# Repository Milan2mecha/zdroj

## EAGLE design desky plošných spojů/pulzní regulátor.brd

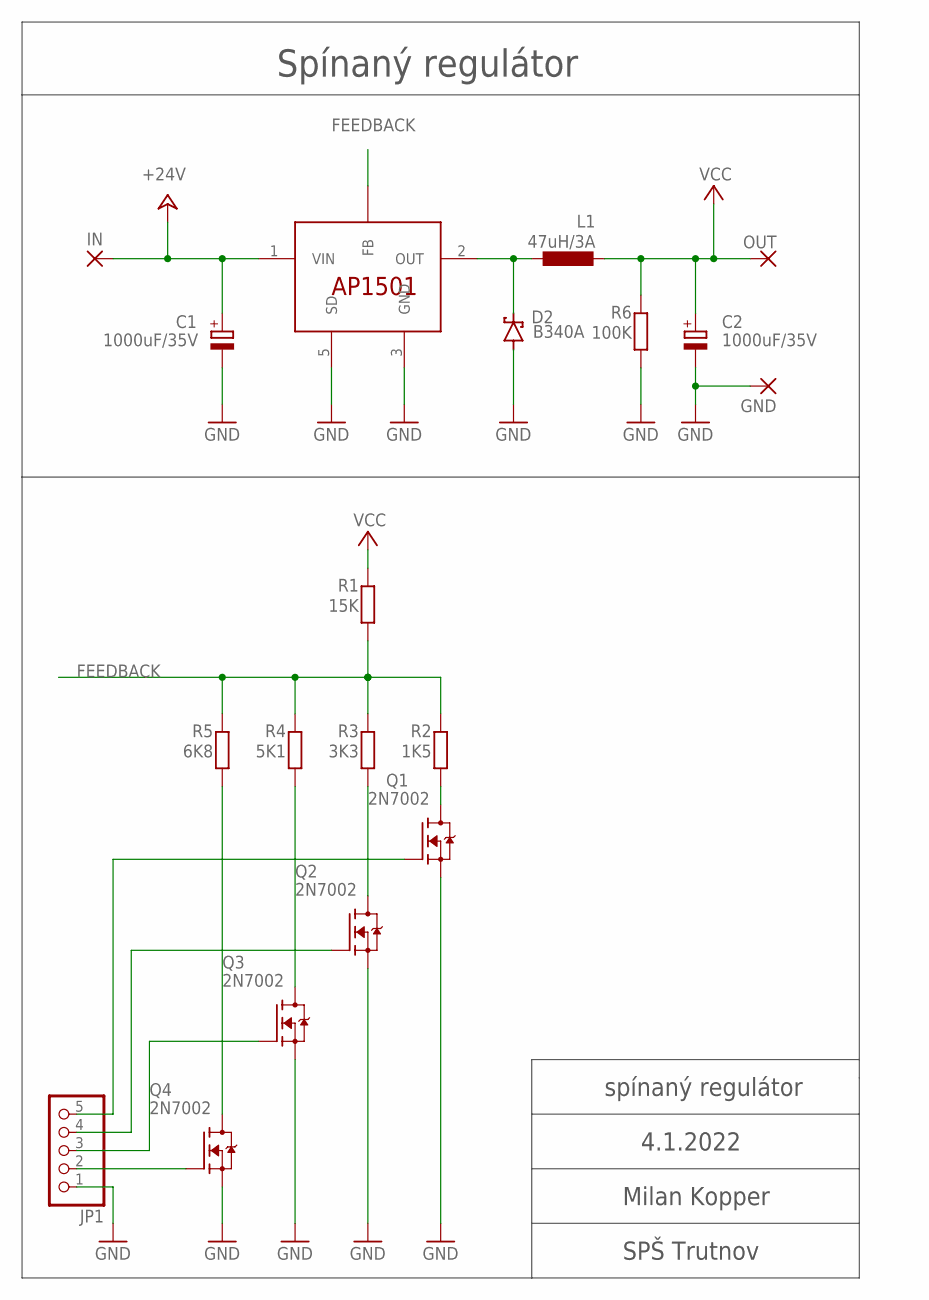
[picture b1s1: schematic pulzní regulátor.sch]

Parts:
C1, C2: 1000uF/35V; E5-10,5
D2: B340A; SMB
GND: 3,17/1,3
IN: 3,17/1,3
JP1: PINHD-1X5; 1X05
L1: 47uH/3A; DTMSS-16/0,033/6,0
OUT: 3,17/1,3
Q1, Q2, Q3, Q4: 2N7002; SOT95P240X110-3N
R1: 15K; R0805
R2: 1K5; R0805
R3: 3K3; R0805
R4: 5K1; R0805
R5: 6K8; R0805
R6: 100K; R0805
U$2: AP1501TO220; TO220-5

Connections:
+24V: C1.+, IN.1, U$2.1 (VIN)
FEEDBACK: R1.1, R2.2, R3.2, R4.2, R5.2, U$2.4 (FB)
GND: C1.-, C2.-, D2.A, GND.1, JP1.1, Q1.2 (S), Q2.2 (S), Q3.2 (S), Q4.2 (S), R6.1, U$2.3 (GND), U$2.5 (SD)
unnamed: Q4.3 (D), R5.1
unnamed: D2.C, L1.P$1 (1), U$2.2 (OUT)
unnamed: JP1.2, Q4.1 (G)
unnamed: Q1.3 (D), R2.1
unnamed: JP1.3, Q3.1 (G)
unnamed: JP1.4, Q2.1 (G)
unnamed: JP1.5, Q1.1 (G)
unnamed: Q2.3 (D), R3.1
unnamed: Q3.3 (D), R4.1
VCC: C2.+, L1.P$2 (2), OUT.1, R1.2, R6.2

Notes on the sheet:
Spínaný regulátor
spínaný regulátor
4.1.2022
Milan Kopper
SPŠ Trutnov

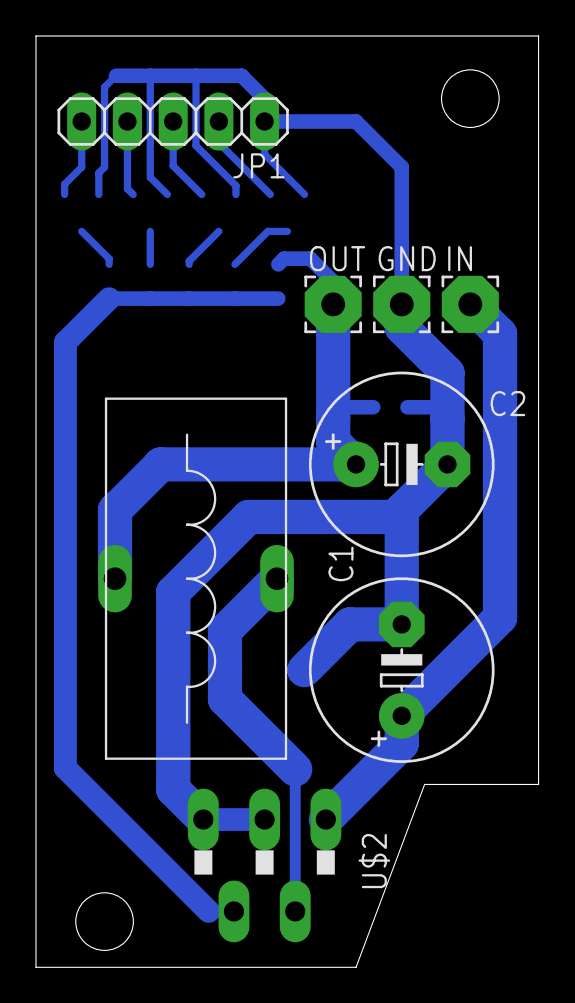
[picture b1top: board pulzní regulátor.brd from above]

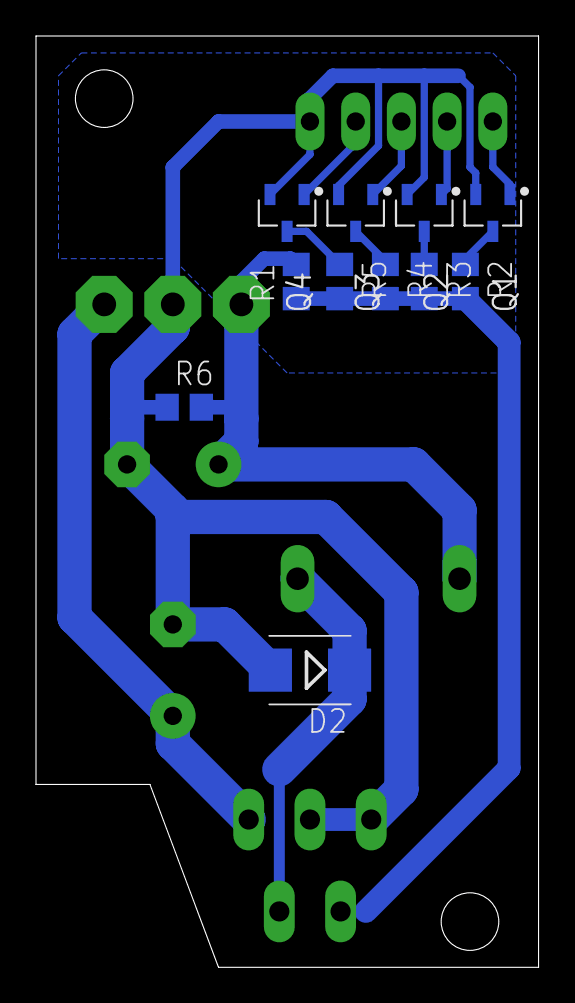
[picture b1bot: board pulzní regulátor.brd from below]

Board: 2 copper layers, 27.9 x 51.7 mm, 19 parts (11 on the bottom side), 13 nets.

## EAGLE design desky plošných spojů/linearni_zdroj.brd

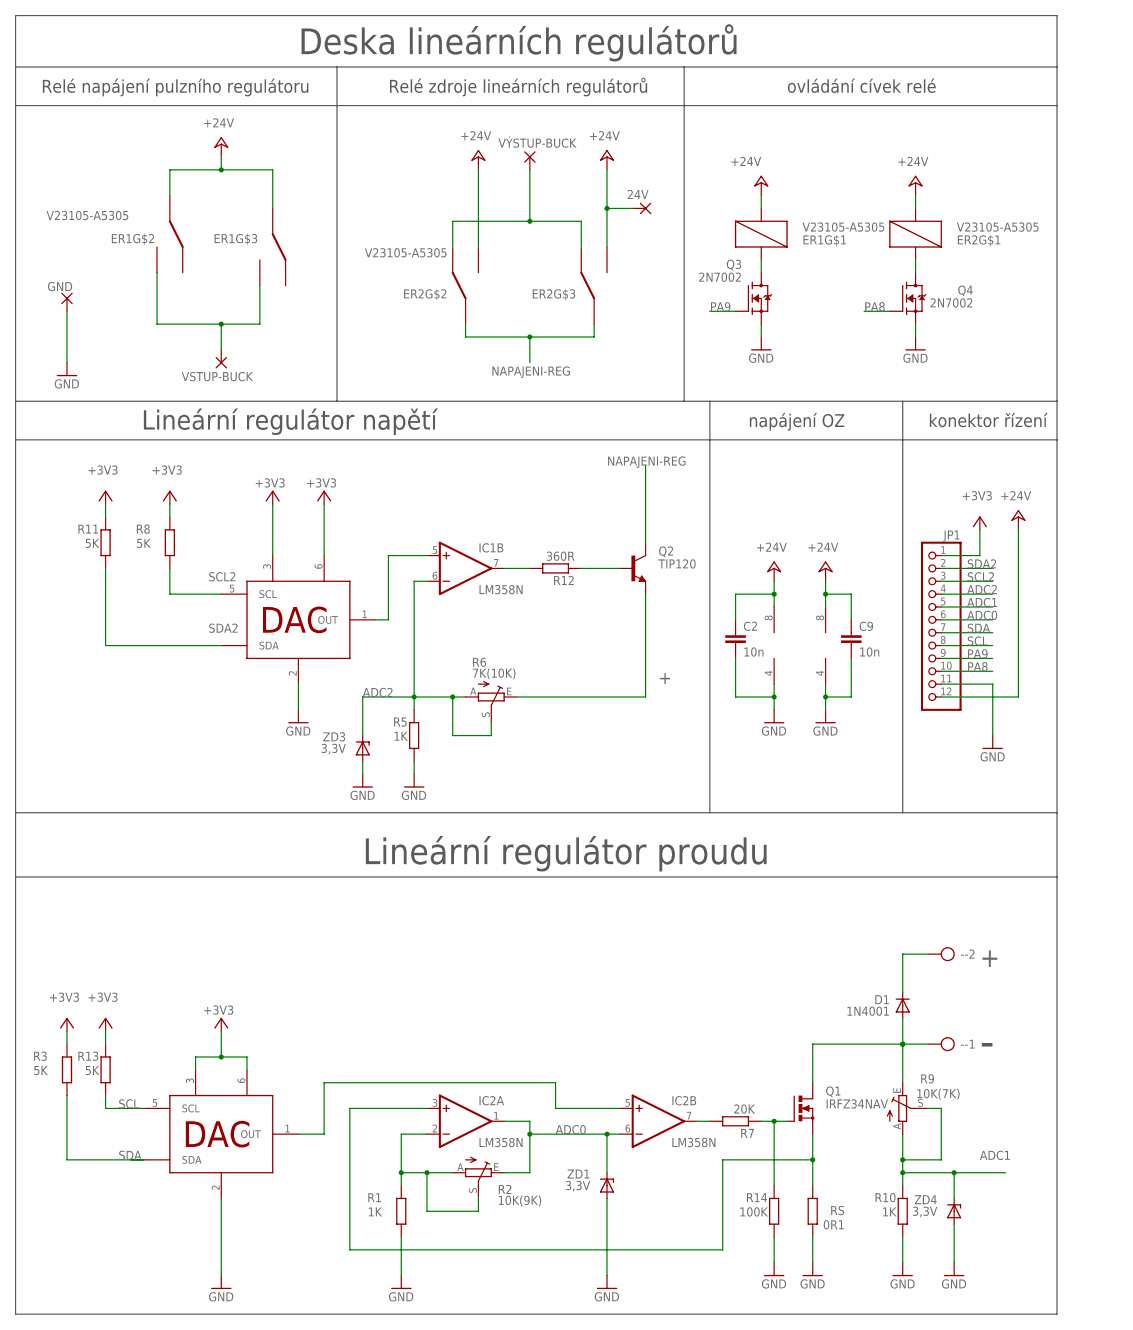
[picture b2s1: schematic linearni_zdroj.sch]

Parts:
24V: 3,81/1,4
-: AK500/2
C2, C9: 10n; C0805
D1: 1N4001; DO35-7B
ER1, ER2: V23105-A5305; V23105-A5305-A201
GND: 3,81/1,4
IC1, IC2: LM358N; DIL08
JP1: PINHD-1X12; 1X12
Q1: IRFZ34NAV; TO220AV
Q2: TIP120; TO220V
Q3, Q4: 2N7002; SOT95P240X110-3N
R1, R5, R10: 1K; R0805
R2: 10K(9K); CA6V
R3, R8, R11, R13: 5K; R0805
R6: 7K(10K); CA6V
R7: 20K; R0805
R9: 10K(7K); CA6V
R12: 360R; R0805
R14: 100K; R0805
RS: 0R1; 0411/15
U$5, U$6: MCP4726; TSOT23-6
VSTUP-BUCK: 3,81/1,4
VÝSTUP-BUCK: 3,81/1,4
ZD1, ZD3, ZD4: 3,3V; MINIMELF

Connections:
+: -.2, D1.C, Q2.3 (E), R6.E
+3V3: JP1.1, R3.2, R8.2, R11.2, R13.2, U$5.3 (VDD), U$5.6 (VREF), U$6.3 (VDD), U$6.6 (VREF)
+24V: 24V.1, C2.1, C9.1, ER1.1, ER1.4 (1), ER1.13 (1), ER2.1, ER2.8 (3), ER2.9 (3), IC1.8 (V+), IC2.8 (V+), JP1.12
ADC0: IC2.1 (OUT), IC2.6 (-IN), JP1.6, R2.E, ZD1.C
ADC1: JP1.5, R9.A, R9.S, R10.2, ZD4.C
ADC2: IC1.6 (-IN), JP1.4, R5.2, R6.A, R6.S, ZD3.C
GND: C2.2, C9.2, GND.1, IC1.4 (V-), IC2.4 (V-), JP1.11, Q3.2 (S), Q4.2 (S), R1.1, R5.1, R10.1, R14.1, RS.1, U$5.2 (VSS), U$6.2 (VSS), ZD1.A, ZD3.A, ZD4.A
unnamed: IC2.7 (OUT), R7.2
unnamed: Q1.G, R7.1, R14.2
unnamed: IC2.2 (-IN), R1.2, R2.A, R2.S
unnamed: Q2.1 (B), R12.1
unnamed: IC2.5 (+IN), U$5.1 (OUT)
unnamed: -.1, D1.A, Q1.D, R9.E
unnamed: IC1.5 (+IN), U$6.1 (OUT)
unnamed: ER2.6 (2), ER2.11 (2), VÝSTUP-BUCK.1
unnamed: IC1.7 (OUT), R12.2
unnamed: ER1.16, Q3.3 (D)
unnamed: ER2.16, Q4.3 (D)
unnamed: ER1.8 (3), ER1.9 (3), VSTUP-BUCK.1
unnamed: IC2.3 (+IN), Q1.S, RS.2
NAPAJENI-REG: ER2.4 (1), ER2.13 (1), Q2.2 (C)
PA8: JP1.10, Q4.1 (G)
PA9: JP1.9, Q3.1 (G)
SCL: JP1.8, R13.1, U$5.5 (SCL)
SCL2: JP1.3, R8.1, U$6.5 (SCL)
SDA: JP1.7, R3.1, U$5.4 (SDA)
SDA2: JP1.2, R11.1, U$6.4 (SDA)

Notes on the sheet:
Lineární regulátor napětí
napájení OZ
Relé zdroje lineárních regulátorů
Relé napájení pulzního regulátoru
konektor řízení
Lineární regulátor proudu
ovládání cívek relé
Deska lineárních regulátorů

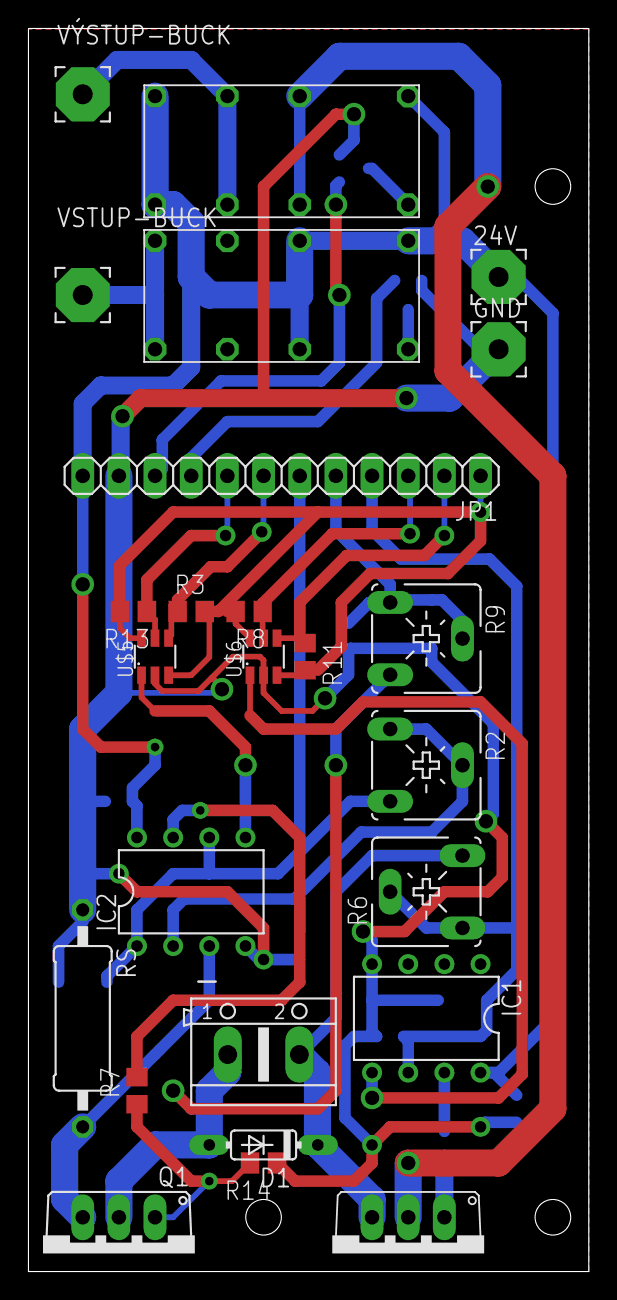
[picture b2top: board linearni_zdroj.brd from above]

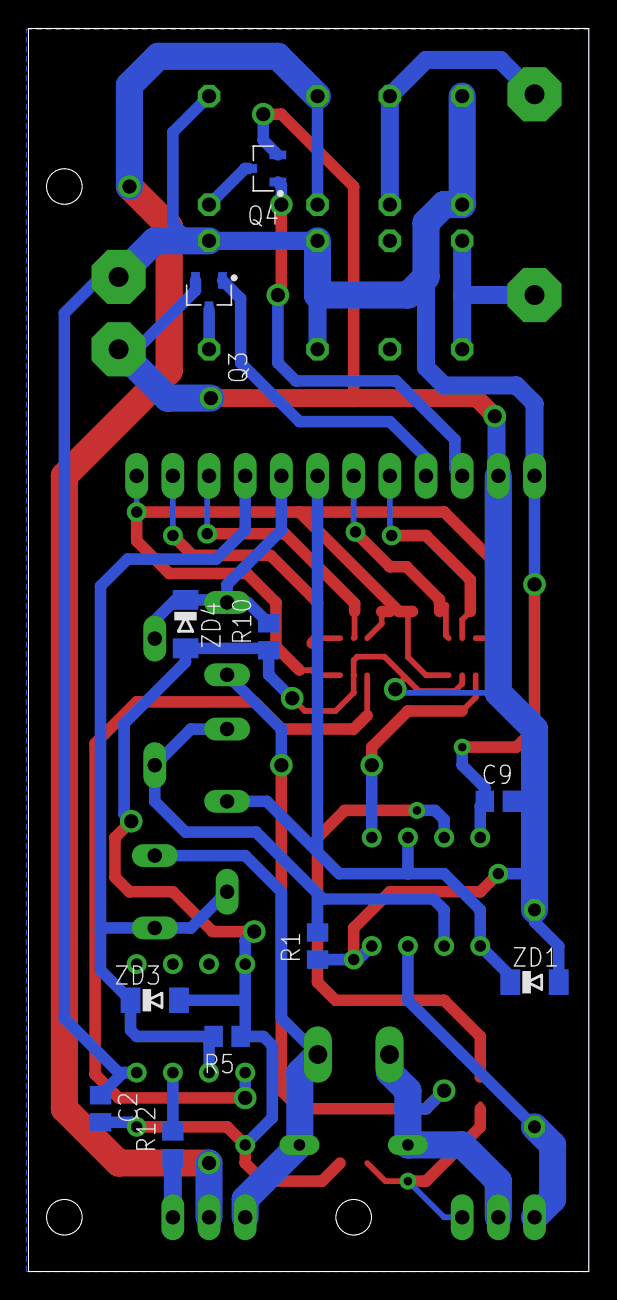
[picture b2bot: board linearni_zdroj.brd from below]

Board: 2 copper layers, 39.4 x 87.3 mm, 36 parts (11 on the bottom side), 27 nets.

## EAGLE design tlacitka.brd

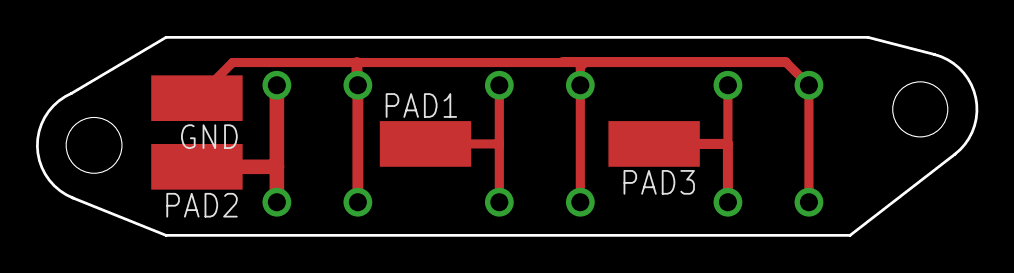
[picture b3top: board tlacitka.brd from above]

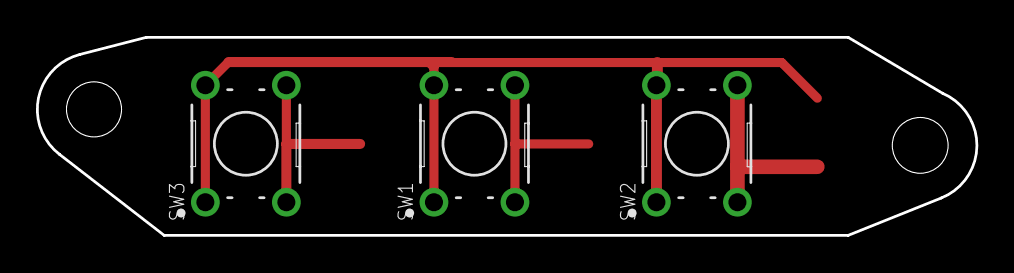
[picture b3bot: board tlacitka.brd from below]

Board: 2 copper layers, 52.2 x 11.0 mm, 7 parts (3 on the bottom side), 4 nets.

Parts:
GND: SMD2,54-5,08
PAD1, PAD2, PAD3: SMD2,54-5,08
SW1, SW2, SW3: B3F-1000

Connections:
unnamed: PAD1.1, SW1.3, SW1.4
unnamed: PAD2.1, SW2.3, SW2.4
unnamed: GND.1, SW1.1, SW1.2, SW2.1, SW2.2, SW3.1, SW3.2
unnamed: PAD3.1, SW3.3, SW3.4

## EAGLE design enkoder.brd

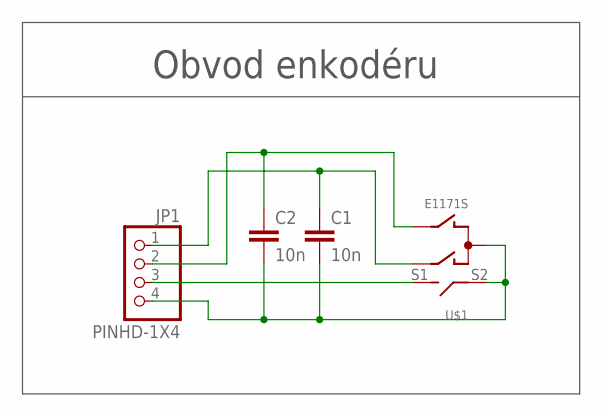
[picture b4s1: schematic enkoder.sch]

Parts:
C1, C2: 10n; C0805
JP1: PINHD-1X4; 1X04
U$1: E1171S

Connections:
unnamed: C1.2, C2.2, JP1.4, U$1.C, U$1.S2
unnamed: JP1.3, U$1.S1
unnamed: C1.1, JP1.1, U$1.A
unnamed: C2.1, JP1.2, U$1.B

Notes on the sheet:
Obvod enkodéru

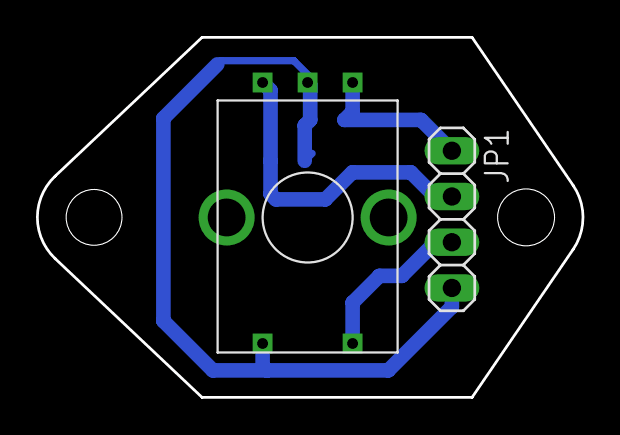
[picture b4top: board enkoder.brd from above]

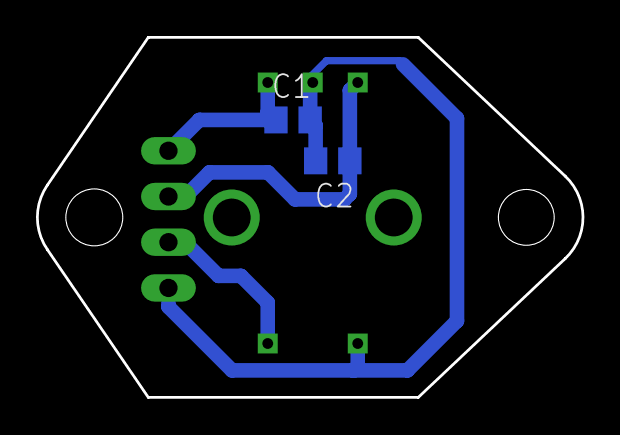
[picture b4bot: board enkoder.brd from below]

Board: 2 copper layers, 30.3 x 20.0 mm, 4 parts (2 on the bottom side), 4 nets.

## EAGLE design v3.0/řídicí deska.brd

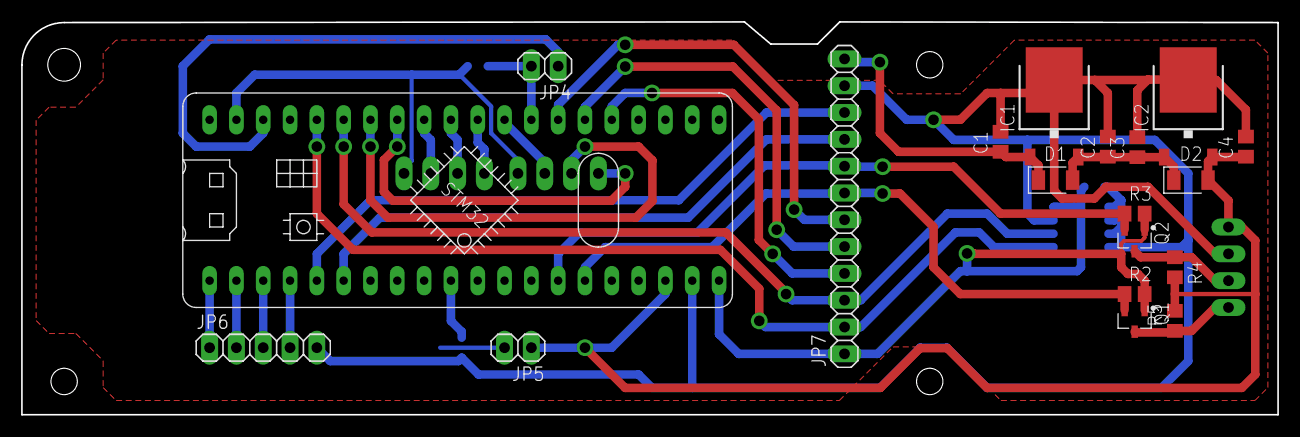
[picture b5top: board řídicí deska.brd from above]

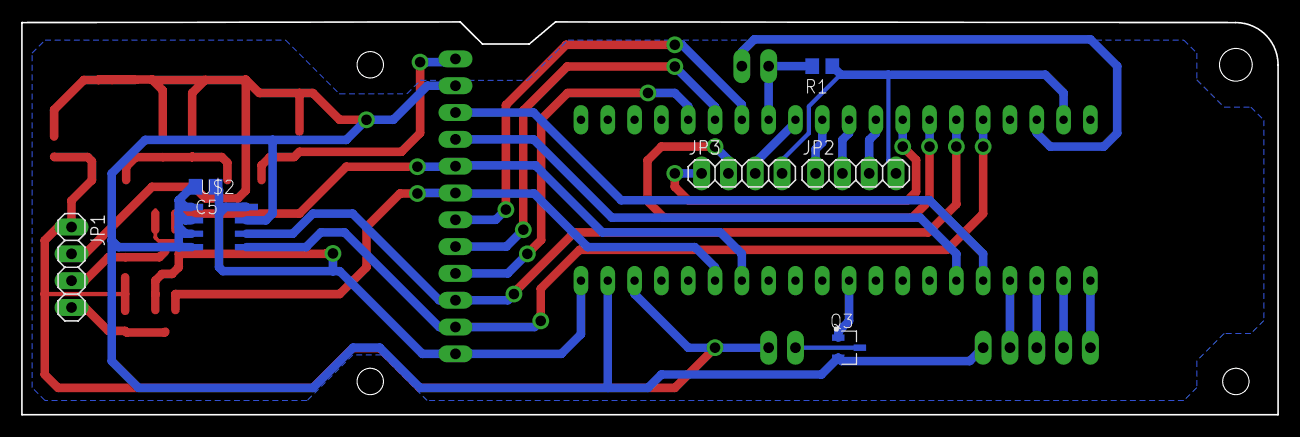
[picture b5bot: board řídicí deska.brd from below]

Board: 2 copper layers, 119.0 x 37.2 mm, 26 parts (7 on the bottom side), 29 nets.

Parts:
C1, C2, C3, C4: 100n; C0805
C5: 10n; C0805
D1, D2: LL4148-GS08; DIOMELF3516
IC1: MC78M12ACDTG; DPACK_3
IC2: AZ1117CD5; DPACK_3
JP1, JP2, JP3: PINHD-1X4; 1X04
JP4, JP5: PINHD-1X2; 1X02
JP6: PINHD-1X5; 1X05
JP7: PINHD-1X12; 1X12
Q1, Q2, Q3: NX3008; SOT95P240X110-3N
R1: 10K; R0805
R2, R3, R4, R5: 5K; R0805
U$1: BLUE_PILL
U$2: M24CXX; SO8

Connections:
+3V3: C5.1, JP4.1, JP7.1, Q1.1, Q2.1, R2.2, R3.2, U$1.P$20, U$1.P$23, U$2.8
+5V: C4.1, D2.2, IC2.3, JP1.1, JP5.1, R4.2, R5.2, U$1.P$18
+12V: C2.1, C3.1, D1.2, D2.1, IC1.3, IC2.1
+24V: C1.1, D1.1, IC1.1, JP7.12
GND: C1.2, C2.2, C3.2, C4.2, C5.2, IC1.4, IC2.4, JP1.2, JP2.4, JP3.4, JP6.5, JP7.11, Q3.2, R1.1, U$1.P$19, U$1.P$21, U$1.P$22, U$2.1, U$2.2, U$2.3, U$2.4, U$2.7
unnamed: JP5.2, Q3.3
unnamed: JP1.3, Q2.3, R4.1
unnamed: JP1.4, Q1.3, R5.1
PA0: JP7.4, U$1.P$36
PA1: JP7.5, U$1.P$35
PA2: JP7.6, U$1.P$34
PA3: JP4.2, R1.2, U$1.P$33
PA4: JP3.3, U$1.P$32
PA5: JP2.1, U$1.P$31
PA6: JP2.2, U$1.P$30
PA7: JP2.3, U$1.P$29
PA8: JP7.10, U$1.P$5
PA9: JP7.9, U$1.P$6
PA15: Q3.1, U$1.P$10
PB0: JP3.1, U$1.P$28
PB1: JP3.2, U$1.P$27
PB12: JP6.1, U$1.P$1
PB13: JP6.2, U$1.P$2
PB14: JP6.3, U$1.P$3
PB15: JP6.4, U$1.P$4
SCL: JP7.8, Q2.2, R3.1, U$1.P$14
SCL2: JP7.3, U$1.P$26, U$2.6
SDA: JP7.7, Q1.2, R2.1, U$1.P$15
SDA2: JP7.2, U$1.P$25, U$2.5

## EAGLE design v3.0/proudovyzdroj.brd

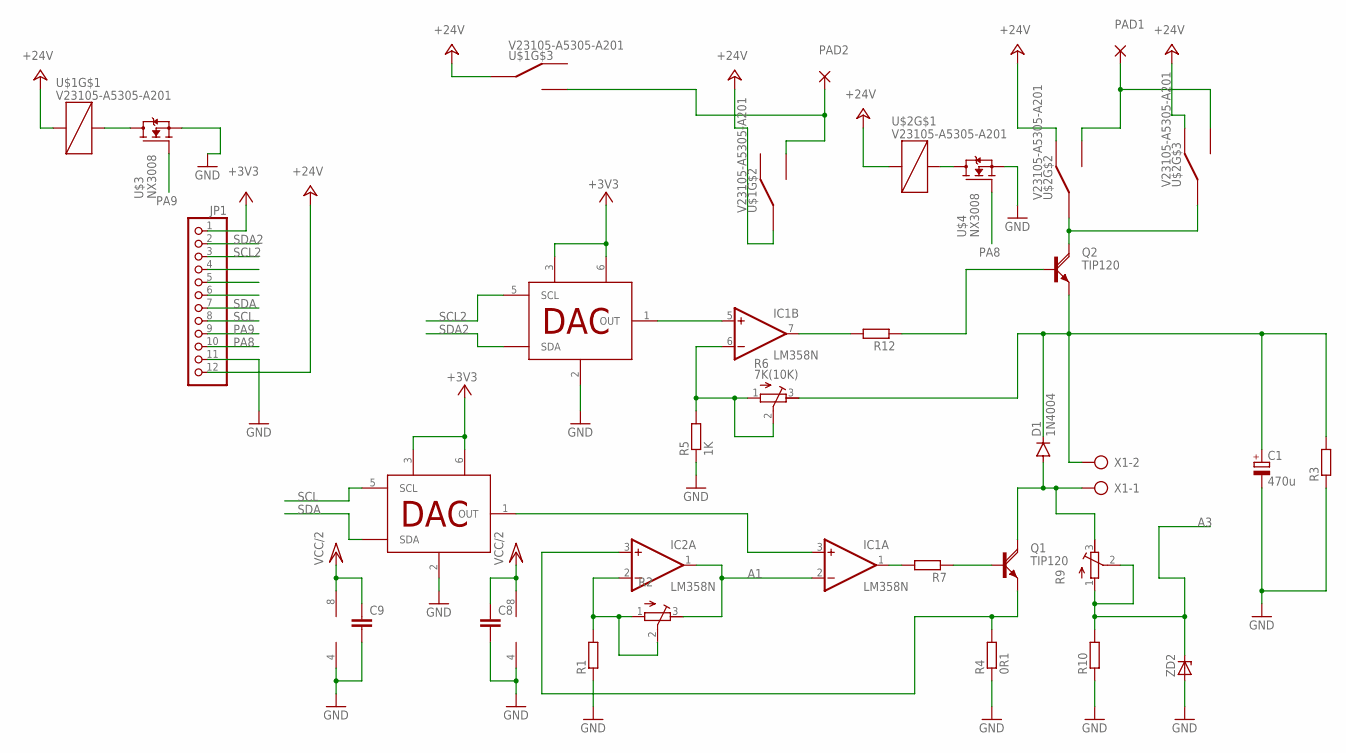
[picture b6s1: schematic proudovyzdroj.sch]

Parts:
C1: 470u; E3,5-8
C8, C9: C-EUC0805; C0805
D1: 1N4004; DO41-10
IC1, IC2: LM358N; DIL08
JP1: PINHD-1X12; 1X12
PAD1, PAD2: 3,81/1,4
Q1, Q2: TIP120; TO220AH
R1: R-EU_M0805; M0805
R2, R9: R-TRIMM3339P; RTRIM3339P
R3, R7, R10, R12: R-EU_R0805; R0805
R4: 0R1; 0411/15
R5: 1K; R0805
R6: 7K(10K); RTRIM3339P
U$1, U$2: V23105-A5305-A201
U$3, U$4: NX3008; SOT95P240X110-3N
U$5, U$6: MCP4726; TSOT23-6
X1: AK500/2
ZD2: DIODE_ZENER5; DO34-5

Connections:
+3V3: JP1.1, U$5.3 (VDD), U$5.6 (VREF), U$6.3 (VDD), U$6.6 (VREF)
+24V: JP1.12, U$1.1, U$1.4 (1), U$1.13 (1), U$2.1, U$2.6 (2), U$2.11 (2)
A1: IC1.2 (-IN), IC2.1 (OUT), R2.3 (E)
A3: R9.1 (A), R9.2 (S), R10.2, ZD2.C
GND: C1.-, C8.2, C9.2, IC1.4 (V-), IC2.4 (V-), JP1.11, R1.1, R3.1, R4.1, R5.1, R10.1, U$3.2 (S), U$4.2 (S), U$5.2 (VSS), U$6.2 (VSS), ZD2.A
unnamed: IC2.3 (+IN), Q1.E, R4.2
unnamed: IC1.1 (OUT), R7.2
unnamed: IC2.2 (-IN), R1.2, R2.1 (A), R2.2 (S)
unnamed: Q2.B, R12.1
unnamed: Q1.B, R7.1
unnamed: IC1.3 (+IN), U$5.1 (OUT)
unnamed: D1.A, Q1.C, R9.3 (E), X1.1
unnamed: Q2.C, U$2.4 (1), U$2.13 (1)
unnamed: IC1.5 (+IN), U$6.1 (OUT)
unnamed: PAD1.1, U$2.8 (3), U$2.9 (3)
unnamed: IC1.6 (-IN), R5.2, R6.1 (A), R6.2 (S)
unnamed: IC1.7 (OUT), R12.2
unnamed: C1.+, D1.C, Q2.E, R3.2, R6.3 (E), X1.2
unnamed: U$1.16, U$3.3 (D)
unnamed: U$2.16, U$4.3 (D)
unnamed: PAD2.1, U$1.8 (3), U$1.9 (3)
PA8: JP1.10, U$4.1 (G)
PA9: JP1.9, U$3.1 (G)
SCL: JP1.8, U$5.5 (SCL)
SCL2: JP1.3, U$6.5 (SCL)
SDA: JP1.7, U$5.4 (SDA)
SDA2: JP1.2, U$6.4 (SDA)
VCC/2: C8.1, C9.1, IC1.8 (V+), IC2.8 (V+)

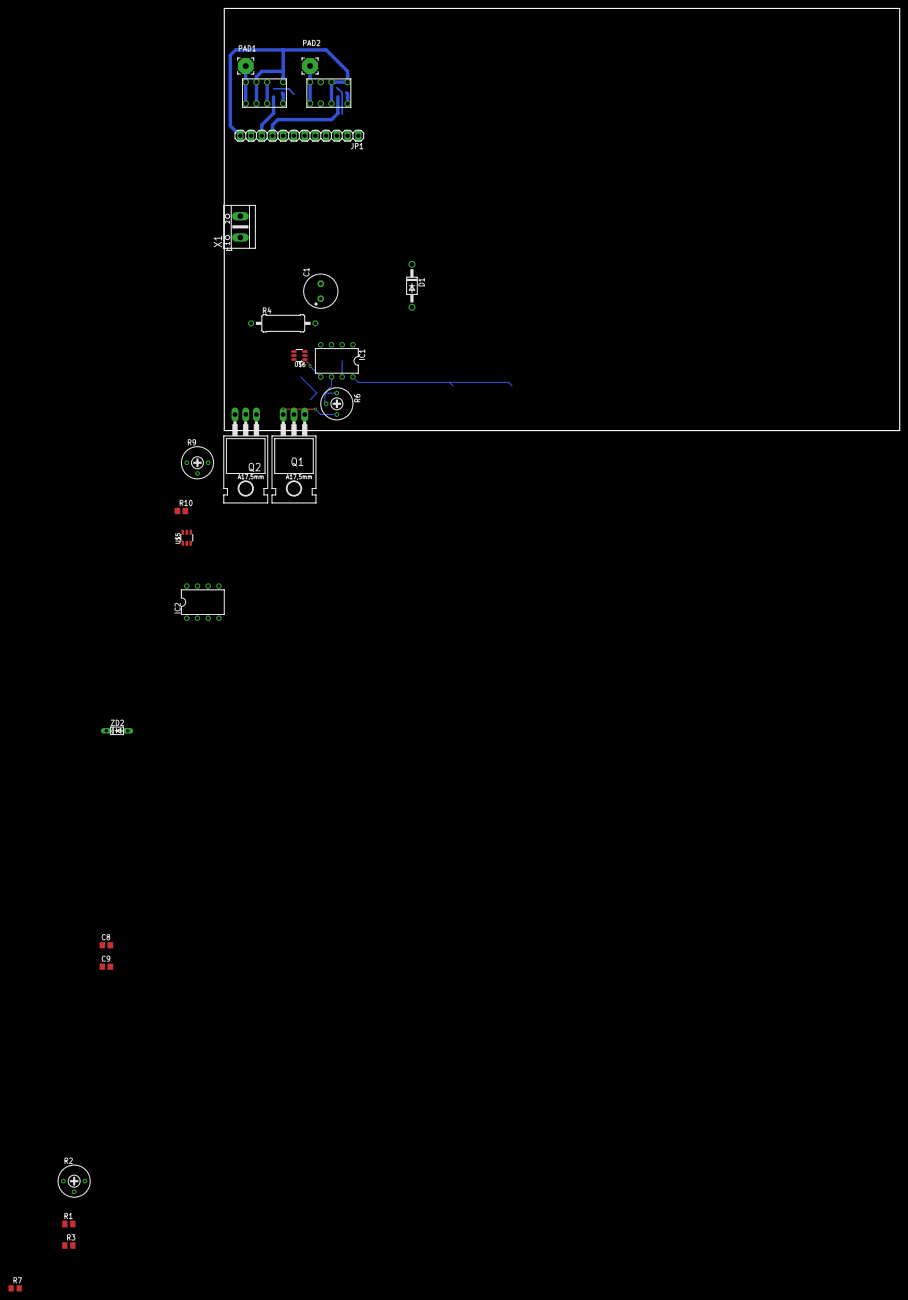
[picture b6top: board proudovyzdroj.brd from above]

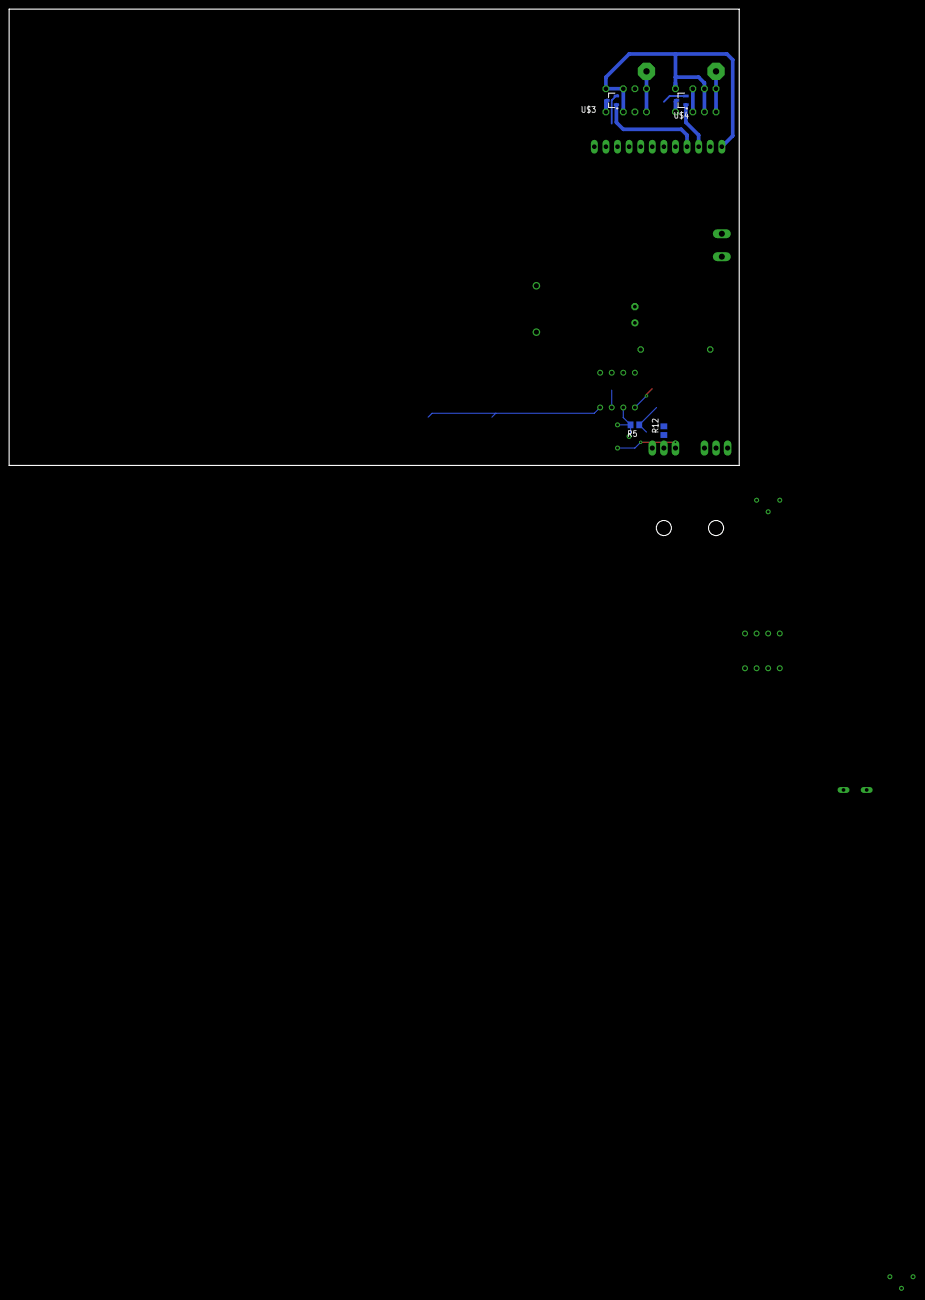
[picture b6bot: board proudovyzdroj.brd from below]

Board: 2 copper layers, 160.0 x 100.0 mm, 29 parts (4 on the bottom side), 28 nets.

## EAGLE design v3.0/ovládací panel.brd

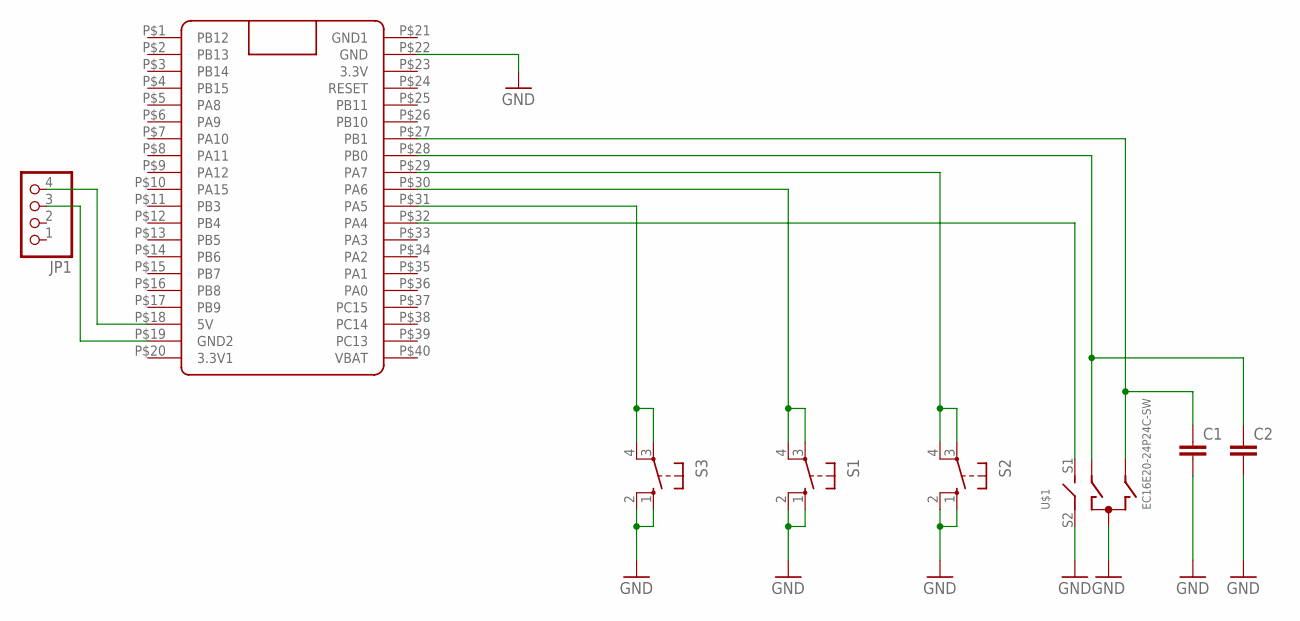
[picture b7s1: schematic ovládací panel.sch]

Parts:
C1, C2: C-EUC0805; C0805
JP1: PINHD-1X4; 1X04
S1, S2, S3: 10-XX; B3F-10XX
U$1: EC16E20-24P24C-SW
U$2: BLUE_PILL

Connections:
GND: C1.2, C2.2, S1.1 (S), S1.2 (S1), S2.1 (S), S2.2 (S1), S3.1 (S), S3.2 (S1), U$1.C, U$1.S2, U$2.P$22 (GND)
GND1: U$2.P$21 (GND1)
unnamed: S3.3, S3.4 (P1), U$2.P$31 (PA5)
unnamed: S1.3, S1.4 (P1), U$2.P$30 (PA6)
unnamed: S2.3, S2.4 (P1), U$2.P$29 (PA7)
unnamed: JP1.4, U$2.P$18 (5V)
unnamed: C2.1, U$1.A, U$2.P$28 (PB0)
unnamed: C1.1, U$1.B, U$2.P$27 (PB1)
unnamed: U$1.S1, U$2.P$32 (PA4)
unnamed: JP1.3, U$2.P$19 (GND2)

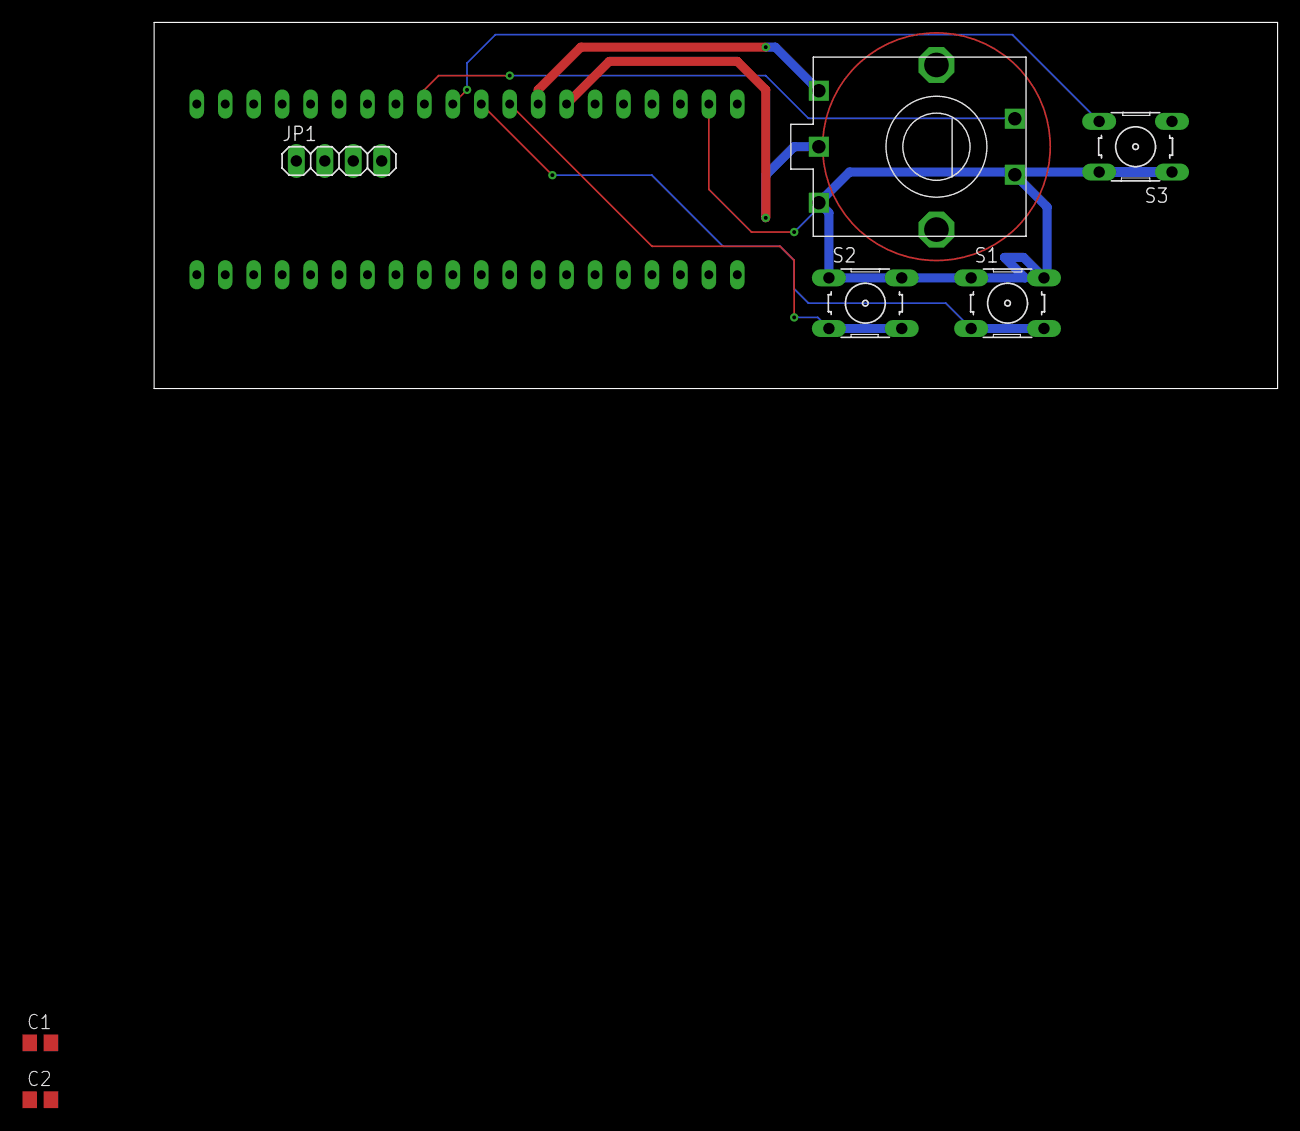
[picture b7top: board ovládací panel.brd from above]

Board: 2 copper layers, 100.3 x 32.7 mm, 8 parts (1 on the bottom side), 9 nets.

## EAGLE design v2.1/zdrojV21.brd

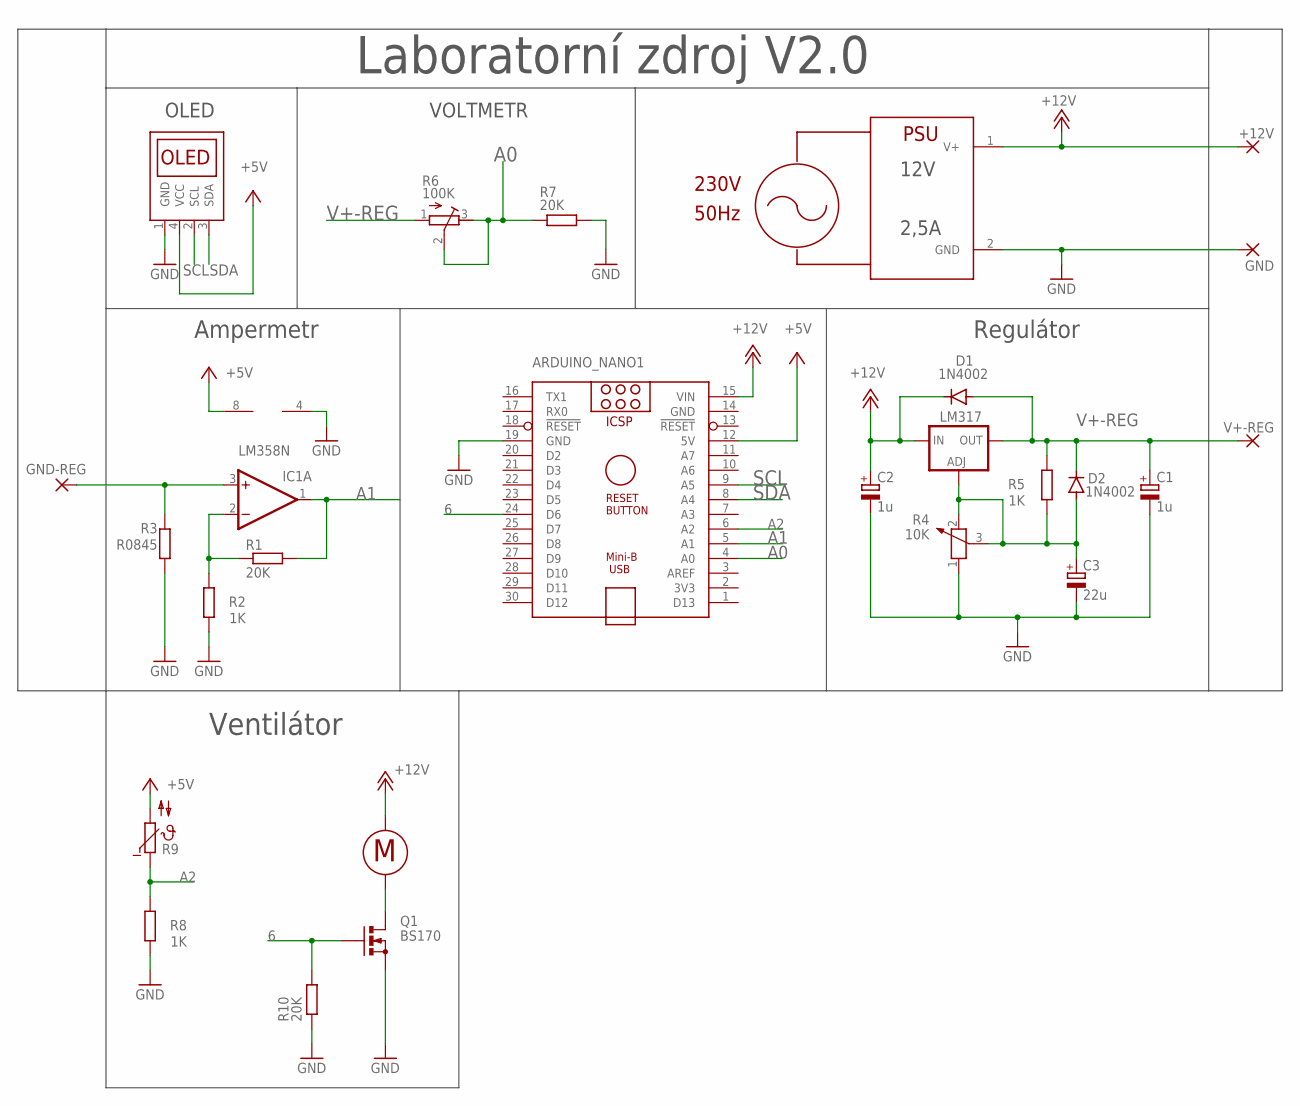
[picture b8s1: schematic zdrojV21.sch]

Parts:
+12V: 3,81/1,4
ARDUINO_NANO1: ARDUINO_NANO
C1, C2: 1u; E2,5-6E
C3: 22u; E2,5-6E
D1, D2: 1N4002; DO41-10
GND: 3,81/1,4
GND-REG: 3,81/1,4
IC1: LM358N; DIL08
IC2: LM317; 317TS
M: KMITOMER; 2PADS
Q1: BS170; SOT54E
R1, R7, R10: 20K; 0204/7
R2, R8: 1K; 0204/7
R3: R0845; 0414V
R4: 10K; PT-10S
R5: 1K; 0207/10
R6: 100K; RTRIM3339P
R9: V642; P642
U$1: OLEDTWII2C; 1X04
U$2: PSU; 1X02
V+-REG: 3,81/1,4

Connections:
6: ARDUINO_NANO1.24 (D6), Q1.G, R10.2
+5V: ARDUINO_NANO1.12 (5V), IC1.8 (V+), R9.2, U$1.4 (VCC)
+12V: +12V.1, ARDUINO_NANO1.15 (VIN), C2.+, D1.C, IC2.3 (IN), M.P$2, U$2.1 (V+)
A0: ARDUINO_NANO1.4 (A0), R6.2 (S), R6.3 (E), R7.1
A1: ARDUINO_NANO1.5 (A1), IC1.1 (OUT), R1.2
A2: ARDUINO_NANO1.6 (A2), R8.2, R9.1
GND: ARDUINO_NANO1.14 (GND), ARDUINO_NANO1.19 (GND), C1.-, C2.-, C3.-, GND.1, IC1.4 (V-), Q1.S, R2.1, R3.1, R4.1, R7.2, R8.1, R10.1, U$1.1 (GND), U$2.2 (GND)
unnamed: IC1.2 (-IN), R1.1, R2.2
unnamed: M.P$1, Q1.D
unnamed: GND-REG.1, IC1.3 (+IN), R3.2
unnamed: C3.+, D2.A, IC2.1 (ADJ), R4.2, R4.3, R5.1
SCL: ARDUINO_NANO1.9 (A5), U$1.2 (SCL)
SDA: ARDUINO_NANO1.8 (A4), U$1.3 (SDA)
V+-REG: C1.+, D1.A, D2.C, IC2.2 (OUT), R5.2, R6.1 (A), V+-REG.1

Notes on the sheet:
Ampermetr
Regulátor
OLED
VOLTMETR
12V
2,5A
Laboratorní zdroj V2.0
Ventilátor

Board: 2 copper layers, 26 parts (0 on the bottom side), 14 nets, no tracks yet.

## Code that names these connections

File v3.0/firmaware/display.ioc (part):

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Mcu.Name=STM32F103C(8-B)Tx
Mcu.Package=LQFP48
Mcu.UserName=STM32F103C8Tx
PA0-WKUP.Signal=ADCx_IN0
PA1.Signal=ADCx_IN1
PA15.Signal=S_TIM2_CH1_ETR
PA2.Signal=ADCx_IN2
PA3.Signal=ADCx_IN3
PA4.GPIOParameters=GPIO_PuPd
PA4.GPIO_PuPd=GPIO_PULLUP
PA4.Signal=GPIO_Input
PA5.GPIOParameters=GPIO_PuPd
PA5.GPIO_PuPd=GPIO_PULLUP
PA5.Signal=GPIO_Input
PA6.GPIOParameters=GPIO_PuPd
PA6.GPIO_PuPd=GPIO_PULLUP
PA6.Signal=GPIO_Input
PA7.GPIOParameters=GPIO_PuPd
PA7.GPIO_PuPd=GPIO_PULLUP
PA7.Signal=GPIO_Input
PA8.Signal=GPIO_Output
PA9.Signal=GPIO_Output
PB0.GPIOParameters=GPIO_PuPd,GPIO_ModeDefaultEXTI
PB0.GPIO_ModeDefaultEXTI=GPIO_MODE_IT_FALLING
PB0.GPIO_PuPd=GPIO_PULLUP
PB0.Signal=GPXTI0
PB1.GPIOParameters=GPIO_PuPd
PB1.GPIO_PuPd=GPIO_PULLUP
PB1.Signal=GPIO_Input
PB10.Mode=I2C
PB10.Signal=I2C2_SCL
PB11.Mode=I2C
PB11.Signal=I2C2_SDA
PB12.Signal=GPIO_Output
PB13.Signal=GPIO_Output
PB14.Signal=GPIO_Output
PB15.Signal=GPIO_Output
PB6.Mode=I2C
PB6.Signal=I2C1_SCL
PB7.Mode=I2C
PB7.Signal=I2C1_SDA
PD0-OSC_IN.Mode=HSE-External-Oscillator
PD0-OSC_IN.Signal=RCC_OSC_IN
PD1-OSC_OUT.Mode=HSE-External-Oscillator
PD1-OSC_OUT.Signal=RCC_OSC_OUT
RCC.SYSCLKFreq_VALUE=72000000
RCC.SYSCLKSource=RCC_SYSCLKSOURCE_PLLCLK
board=custom

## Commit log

2021-04-14 výkres
2021-04-17 funkční kód volt + amper metr
2021-07-10 začátek prací na přidání ventilátoru
2021-07-10 funkční verze 1
2021-12-07 pokračování v základním návrhu
2021-12-07 Základní vize zdroje v3.0
2021-12-10 základní schéma
2021-12-18 náznak řízení spínané části, úklid schématu
2021-12-20 yoink
2021-12-21 page1 demo
2021-12-21 Oprava chyby s posunem kurzotu
2021-12-22 dokončení menu strany 1, přidány CC VC ikony
2021-12-29 vytvořen modul stavitelného buck regulátoru
2022-01-03 přidání řízení DAC1 a ADC
2022-01-03 přepsáno na DMA ADC
2022-01-03 přejmenování složek
2022-01-04 přidáno dynamické obnovování snímků, zahájeny práce na teploměru
2022-01-04 přidán hmatník encoderu
2022-01-04 změna HW config a jiné menší změny
2022-01-05 přidány tlačítka a jejich debounce
2022-01-05 funkční navigace v menu 1
2022-01-05 předběžné menu2
2022-01-06 přidán kód encodéru (bug: nahodně začne řídit cifru na které není cursor)
2022-01-09 funkční NTC teploměr
2022-01-10 funkční regulace ventilátoru s výpisem do menu
2022-01-10 přidány kometáře, opravena chyba výpočtu děliče spínaného zdroje
2022-01-11 opravena chyba pozice kurzoru v menu 1, změněn clock na externí, include knihoven eaglu.
2022-01-12 Voila a enkodér funguje
2022-01-17 přenesení do fusionu
2022-01-17 export frontpanelu z fusionu
2022-01-17 Úprava BUCK regulátoru z 6A na 3A, osnova dokumentace
2022-01-18 regulováný zdroj pro 3A kompletní + dokumentace ovládacího panelu
2022-01-19 mírné úpravy dokumentace, přidání funkce pro zakázané stavy
2022-01-19 Počátek funkce start
2022-01-20 přidána rozlévaná měď, rozšířena dokumentace
2022-01-23 Přidán obvod řízení výběru zdroje lineárního regulátoru
2022-01-23 přejmenování desky
2022-01-26 zpřehlednění schématu
2022-01-28 přidáno základní řízení spínaného zdroje
2022-01-28 přidány pull-up rezistory I2C
2022-01-29 přepracování mainu
2022-01-29 error kódy 2-4
2022-02-02 oprava mosfet ventilátoru
2022-02-04 zpřehledněno schéma spínaného zdroje a dokončena jeho dokumentace
2022-02-06 deska lineárního regulátoru
2022-02-07 přidání 3D modelu úpravy dokumentace
2022-02-08 upratování schémy, dokumentace lineárního regulátoru napětí
2022-02-09 kryty zdroje
2022-02-10 zase sem se jednou ve škole něco naučil
2022-02-10 zase chybka a pokračování v doku
2022-02-12 neumím malovat XD
2022-02-12 vyzuální úprava knihovny
2022-02-12 pokračování v doku úklid schéma
2022-02-14 Be my valentine From: Milan To: SOČka
2022-02-19 Opravena nekomabilita s HW stále přetrvávají chyby mód 1 a korekce napětí
2022-02-20 Opravena chyba módu 1
2022-02-22 měření chyby ADC převodníku
2022-02-22 oddělení od předchozích verzí zdroje
2022-02-22 Dokumentace ADC
2022-02-22 Porekce ADC změna podmínek refresh
2022-02-23 Trochu integrace ještě nikoho nezabilo
2022-02-24 Psát během 3. světový SOČku? Celkem produktivní ne?
2022-02-27 doku
2022-03-02 Po korektůře
2022-03-02 debug
2022-03-03 přejmenovávání a finální úpravy
2022-03-03 Poslední finalizace, začátek práce na prezentaci
2022-03-03 přejmenování
2022-03-03 prezentace
2023-04-14 První verze zadního krytu s výstupem pro USB
2023-04-23 PoC test serialu
2023-04-23 gitignore
2023-05-01 Test layout
2023-05-01 Úklid adresáře
2023-05-01 Funkční seriová komunikace bez ošetření poruchových stavů
2023-05-06 Vytvořen skelet SW
2023-05-08 Příjem seriové komunikace
2023-05-26 Refresh napětí při čtení portu
2023-05-26 Výkon a proud
2023-05-28 Kompletně funkční příjem
2023-06-02 Redesign
2023-06-18 Ikona aplika, tlačítkapro běžná napětí
2023-06-23 sestavení packetu k odeslání
2023-06-30 Uprava FW pro příjímání a odesílání přes USB, nefunkční měření teploty
2023-07-01 Finální funkční úpravy.
2023-07-01 Přidání komentářů
2023-07-01 Přidání dokumentace semestrální práce a videoprezentace
